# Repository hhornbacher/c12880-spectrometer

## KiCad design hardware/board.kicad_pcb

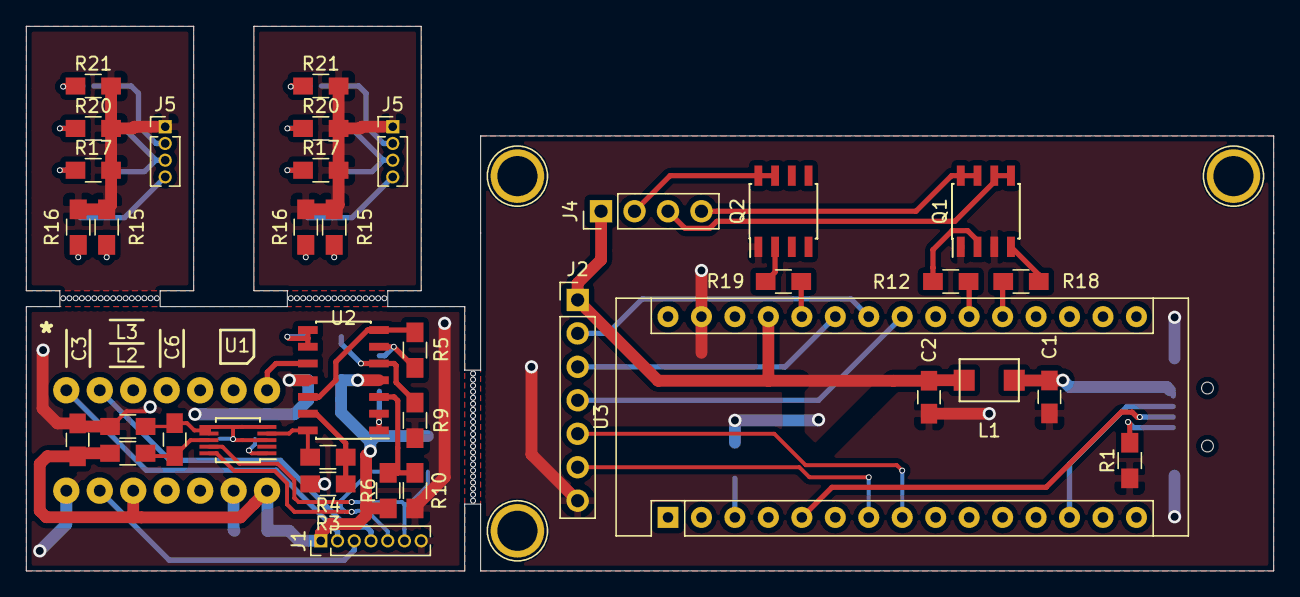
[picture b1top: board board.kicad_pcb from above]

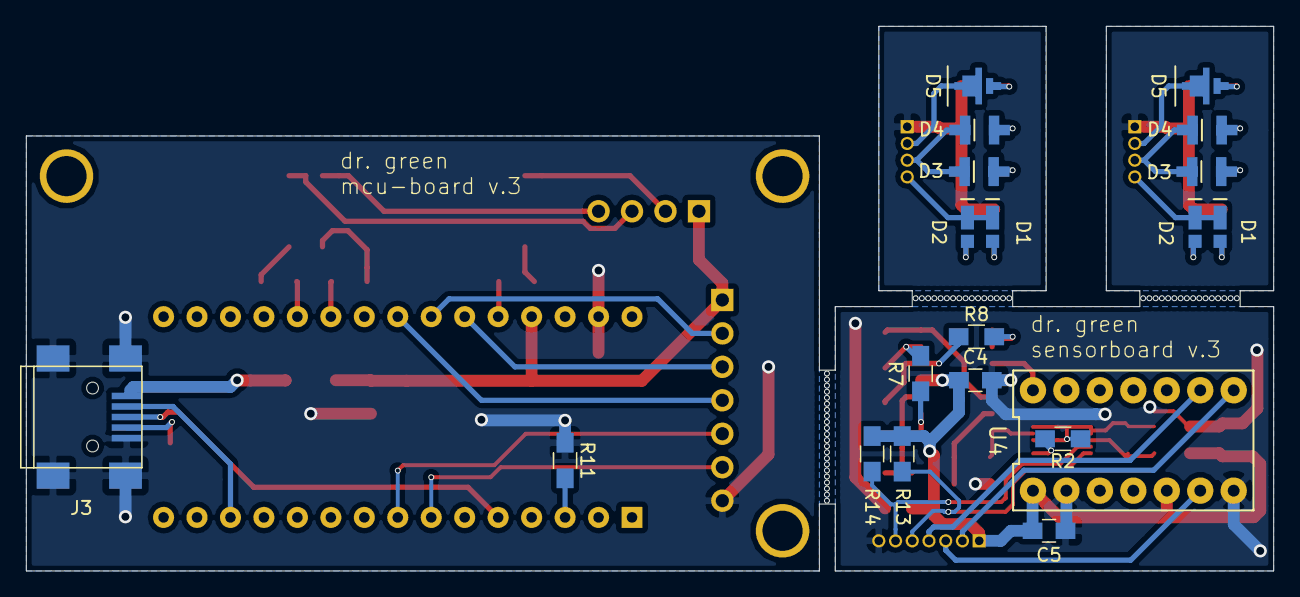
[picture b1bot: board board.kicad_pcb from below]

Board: 2 copper layers, 94.7 x 41.3 mm, 57 parts (20 on the bottom side), 38 nets.

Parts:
C1, C2: 10u; C_0805_HandSoldering
C3, C6: 1u; C_0805_HandSoldering
C4, C5: 100n; C_0805_HandSoldering
D1, D1#2, D2, D2#2: LED; GW-JCLPS2.CM
D3, D3#2, D4, D4#2: LED; LED-OCU-400
D5, D5#2: LED; SFH4776_footprint
J1: Conn_01x07; Pin_Header_Straight_1x07_Pitch1.27mm
J2: Conn_01x07; Pin_Header_Straight_1x07_Pitch2.54mm
J3: USB_OTG; USB_Mini-B
J4: Conn_01x04; Pin_Header_Straight_1x04_Pitch2.54mm
J5, J5#2: Conn_01x04; Pin_Header_Straight_1x04_Pitch1.27mm
L1: 100u; WE-744766920
L2, L3: Ferrite_Bead; L_0805_HandSoldering
Q1, Q2: IRF7311; SOIC-8_3.9x4.9mm_Pitch1.27mm
R1, R3, R6: 100k; R_0805_HandSoldering
R2, R11, R13, R14: 10k; R_0805_HandSoldering
R4, R10: 18k; R_0805_HandSoldering
R5, R7, R8, R9: 1k; R_0805_HandSoldering
R12, R18, R19: 100; R_0805_HandSoldering
R15, R15#2, R16, R16#2, R17, R17#2, R20, R20#2, R21, R21#2: R; R_0805_HandSoldering
U1: ADS1115; VSSOP-10_3x3mm_Pitch0.5mm
U2: MCP6004; SOIC-14_3.9x8.7mm_Pitch1.27mm
U3: NUCLEO-L432KC; Arduino_Nano
U4: C12880MA; DIP-14_0

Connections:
+5V: C2.1, C3.1, C4.1, C5.1, J1.1, J2.1, J4.1, J5.1, J5#2.1, L1.1, L2.1, R6.2, R13.2, R14.2, R15.2, R15#2.2, R16.2, R16#2.2, R17.2, R17#2.2, R20.2, R20#2.2, R21.2, R21#2.2, U2.4, U3.27, U4.1, U4.5
/LED1: D1.1, D1#2.1, D2.1, D2#2.1, J4.4, J5.4, J5#2.4, Q1.7, Q1.8
/LED1_PWM: R12.2, U3.21
/LED2: D3.1, D3#2.1, D4.1, D4#2.1, J4.3, J5.3, J5#2.3, Q1.5, Q1.6
/LED2_PWM: R18.2, U3.20
/LED3: D5.1, D5#2.1, J4.2, J5.2, J5#2.2, Q2.7, Q2.8
/LED3_PWM: R19.2, U3.26
/SCL: J1.5, J2.5, R13.1, U1.10, U3.8
/SDA: J1.6, J2.6, R14.1, U1.9, U3.7
/SENSOR_CLK: J1.3, J2.3, U3.25, U4.6
/SENSOR_START: J1.2, J2.2, U3.24, U4.8
/SENSOR_TRIG: J1.4, J2.4, U3.23, U4.9
/SENSOR_VIDEO: U2.10, U4.14
/USB_DM: J3.2, U3.13
/USB_DP: J3.3, U3.5
/VIDEO_OUT: R4.2, U1.4, U2.14
GND: C1.2, C2.2, C3.2, C4.2, C5.2, J1.7, J2.7, J3.5, J3.6, L3.2, Q1.1, Q1.3, Q2.1, R1.1, R3.1, R9.1, R10.1, R11.1, U2.11, U3.29, U4.2, U4.7
unnamed: C6.1, L3.1, R2.1, U1.3, U1.5, U1.6, U1.7
unnamed: C6.2, L2.2, U1.8
unnamed: D1.2, D1#2.2, R16.1, R16#2.1
unnamed: D2.2, D2#2.2, R15.1, R15#2.1
unnamed: D3.2, D3#2.2, R17.1, R17#2.1
unnamed: D4.2, D4#2.2, R20.1, R20#2.1
unnamed: D5.2, D5#2.2, R21.1, R21#2.1
unnamed: J3.4, R1.2
unnamed: Q1.2, R12.1
unnamed: Q1.4, R18.1
unnamed: Q2.2, R19.1
unnamed: R2.2, U1.1
unnamed: R3.2, R4.1, U2.13
unnamed: R5.1, R7.1, U2.6
unnamed: R5.2, U2.7, U2.12
unnamed: R7.2, U2.1, U2.2
unnamed: R8.1, R9.2, U2.5
unnamed: R8.2, U2.8, U2.9
unnamed: R6.1, R10.2, U2.3
unnamed: R11.2, U3.3
VDD: C1.1, J3.1, L1.2

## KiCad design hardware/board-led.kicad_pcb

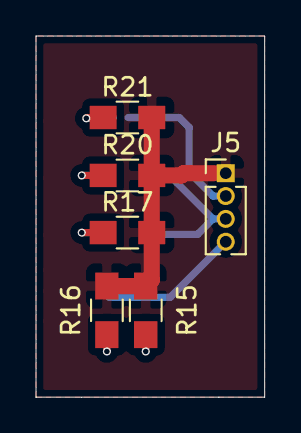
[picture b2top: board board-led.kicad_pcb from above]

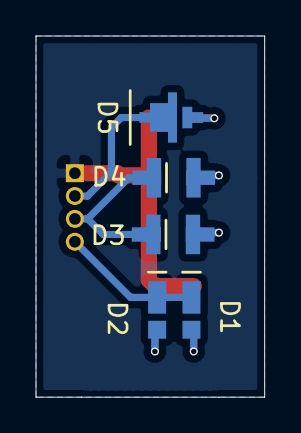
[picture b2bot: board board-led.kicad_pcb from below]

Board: 2 copper layers, 12.7 x 20.1 mm, 11 parts (5 on the bottom side), 9 nets.

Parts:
D1, D2: LED; GW-JCLPS2.CM
D3, D4: LED; LED-OCU-400
D5: LED; SFH4776_footprint
J5: Conn_01x04; Pin_Header_Straight_1x04_Pitch1.27mm
R15, R16, R17, R20, R21: R; R_0805_HandSoldering

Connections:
+5V: J5.1, R15.2, R16.2, R17.2, R20.2, R21.2
/LED1: D1.1, D2.1, J5.4
/LED2: D3.1, D4.1, J5.3
/LED3: D5.1, J5.2
unnamed: D1.2, R16.1
unnamed: D2.2, R15.1
unnamed: D3.2, R17.1
unnamed: D4.2, R20.1
unnamed: D5.2, R21.1

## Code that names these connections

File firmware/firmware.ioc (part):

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Mcu.Name=STM32L432K(B-C)Ux
Mcu.Package=UFQFPN32
Mcu.UserName=STM32L432KCUx
PA0.GPIOParameters=GPIO_Label
PA0.GPIO_Label=MCO [High speed clock in]
PA0.Mode=HSE-External-Clock-Source-for-LittleOrca
PA0.Signal=RCC_CK_IN
PA1.Signal=GPIO_Output
PA10.Mode=I2C
PA10.Signal=I2C1_SDA
PA11.Mode=Device
PA11.Signal=USB_DM
PA12.Mode=Device
PA12.Signal=USB_DP
PA13\ (JTMS-SWDIO).GPIOParameters=GPIO_Label
PA13\ (JTMS-SWDIO).GPIO_Label=SWDIO
PA13\ (JTMS-SWDIO).Mode=Serial_Wire
PA13\ (JTMS-SWDIO).Signal=SYS_JTMS-SWDIO
PA14\ (JTCK-SWCLK).GPIOParameters=GPIO_Label
PA14\ (JTCK-SWCLK).GPIO_Label=SWCLK
PA14\ (JTCK-SWCLK).Mode=Serial_Wire
PA14\ (JTCK-SWCLK).Signal=SYS_JTCK-SWCLK
PA2.Signal=GPIO_Output
PA3.GPIOParameters=GPIO_Speed,GPIO_Label
PA3.GPIO_Label=LED_PWM_WHITE
PA3.GPIO_Speed=GPIO_SPEED_FREQ_VERY_HIGH
PA3.Signal=S_TIM2_CH4
PA4.GPIOParameters=GPIO_Label
PA4.GPIO_Label=SENSOR_EOS
PA4.Signal=GPIO_Input
PA5.GPIOParameters=GPIO_Label
PA5.GPIO_Label=SENSOR_TRIG
PA5.Signal=GPXTI5
PA6.GPIOParameters=GPIO_Label
PA6.GPIO_Label=SENSOR_START
PA6.Signal=GPIO_Output
PA7.GPIOParameters=GPIO_Label
PA7.GPIO_Label=SENSOR_CLK
PA7.Mode=PWM Generation1 CH1N
PA7.Signal=TIM1_CH1N
PA9.Mode=I2C
PA9.Signal=I2C1_SCL
PB3\ (JTDO-TRACESWO).GPIOParameters=GPIO_Label
PB3\ (JTDO-TRACESWO).GPIO_Label=LD3 [Green]
PB3\ (JTDO-TRACESWO).Signal=GPIO_Output
PC14-OSC32_IN\ (PC14).Mode=LSE-External-Oscillator
PC14-OSC32_IN\ (PC14).Signal=RCC_OSC32_IN
PC15-OSC32_OUT\ (PC15).Mode=LSE-External-Oscillator
PC15-OSC32_OUT\ (PC15).Signal=RCC_OSC32_OUT
RCC.HSE_VALUE=8000000
RCC.SYSCLKFreq_VALUE=64000000
RCC.SYSCLKSource=RCC_SYSCLKSOURCE_PLLCLK
board=NUCLEO-L432KC
boardIOC=true

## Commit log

2018-12-05 add firmware
